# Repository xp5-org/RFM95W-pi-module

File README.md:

# RFM95W-pi-module
PCB to connect RFM95W module to ras pi header

have not tested it yet, need to verify things are wired correctly and pinouts are correct

I set this up to be buildable on a single-layer routed or etched (home made) pcb . 

it relies upon jumper bodge wires to complete some of the wiring, otherwise this would be better served by at least 2 layers or 4 layers board.

ras pi zero has two SPI channels, which can allow up to two simutaenous radios/modems in use. 

<br>
<br>

## single radio layout ##

<br>
<br>

## dual radio layout ##

<br>
<br>

# converting kicad gerbers to G-code for CNC
http://flatcam.org/download

need to generate the isolation path (mill the PCB) and then generate the drill instructions (through-holes and vias drills) separately

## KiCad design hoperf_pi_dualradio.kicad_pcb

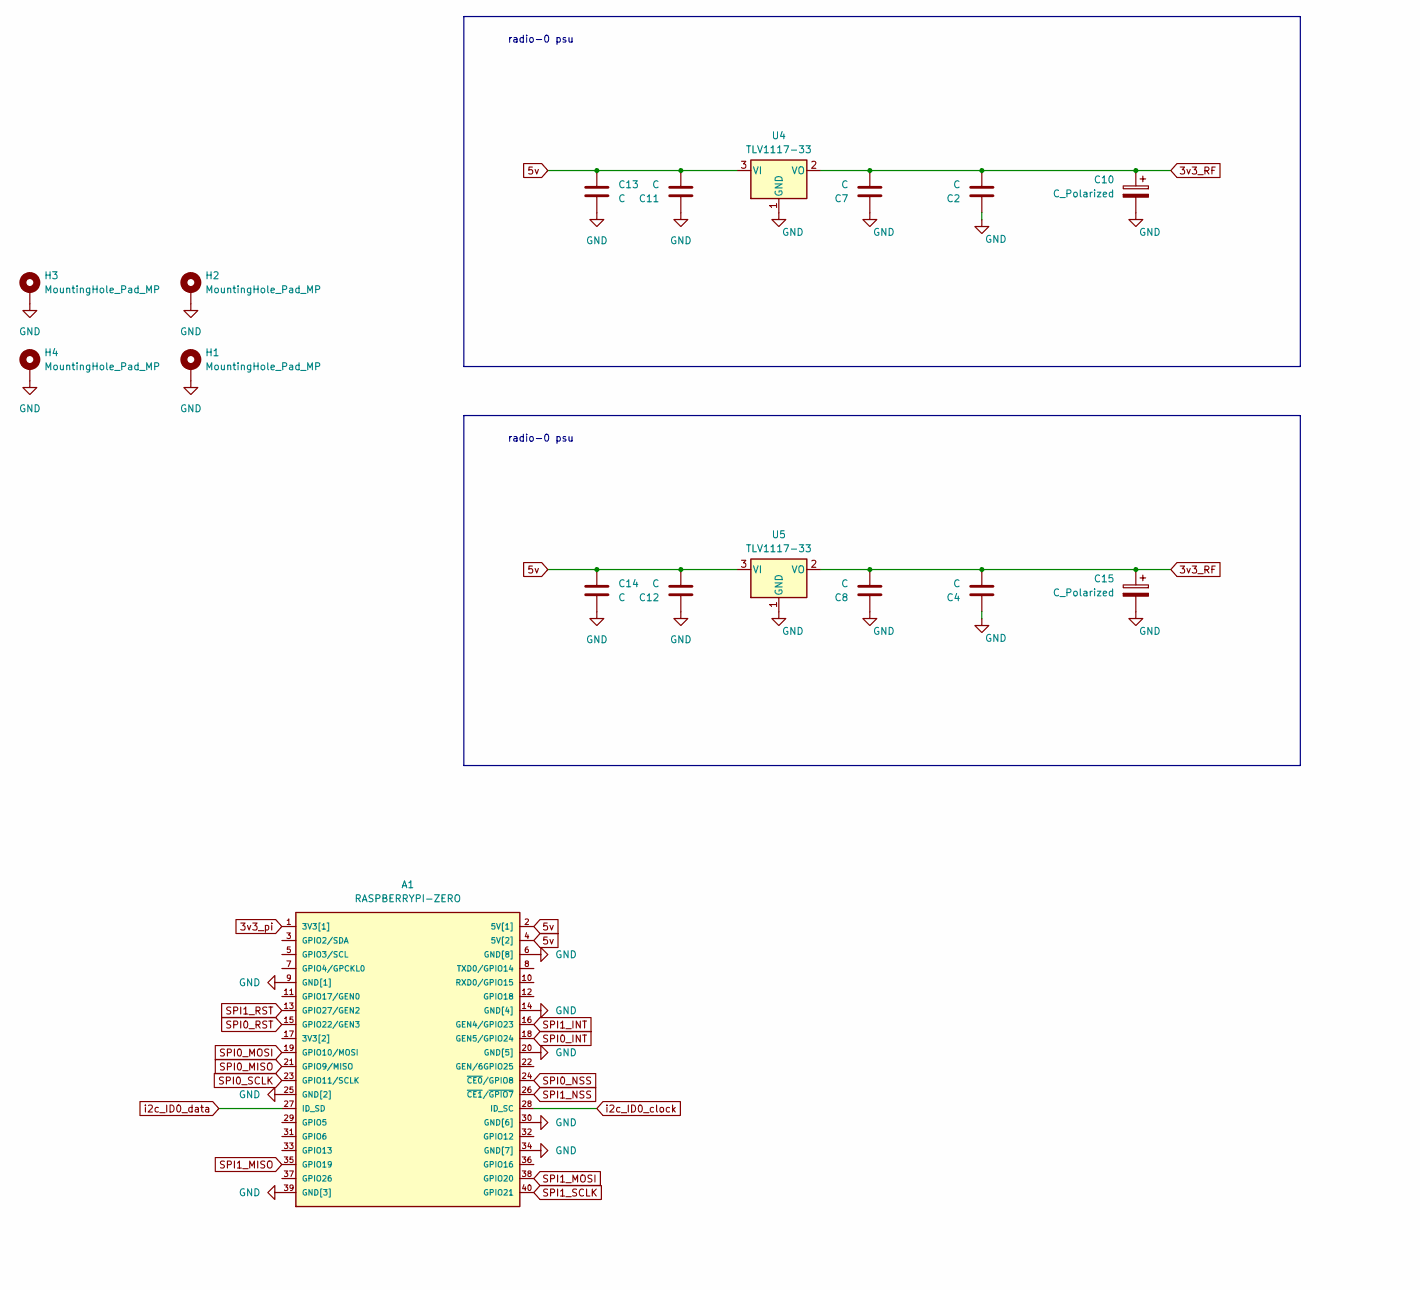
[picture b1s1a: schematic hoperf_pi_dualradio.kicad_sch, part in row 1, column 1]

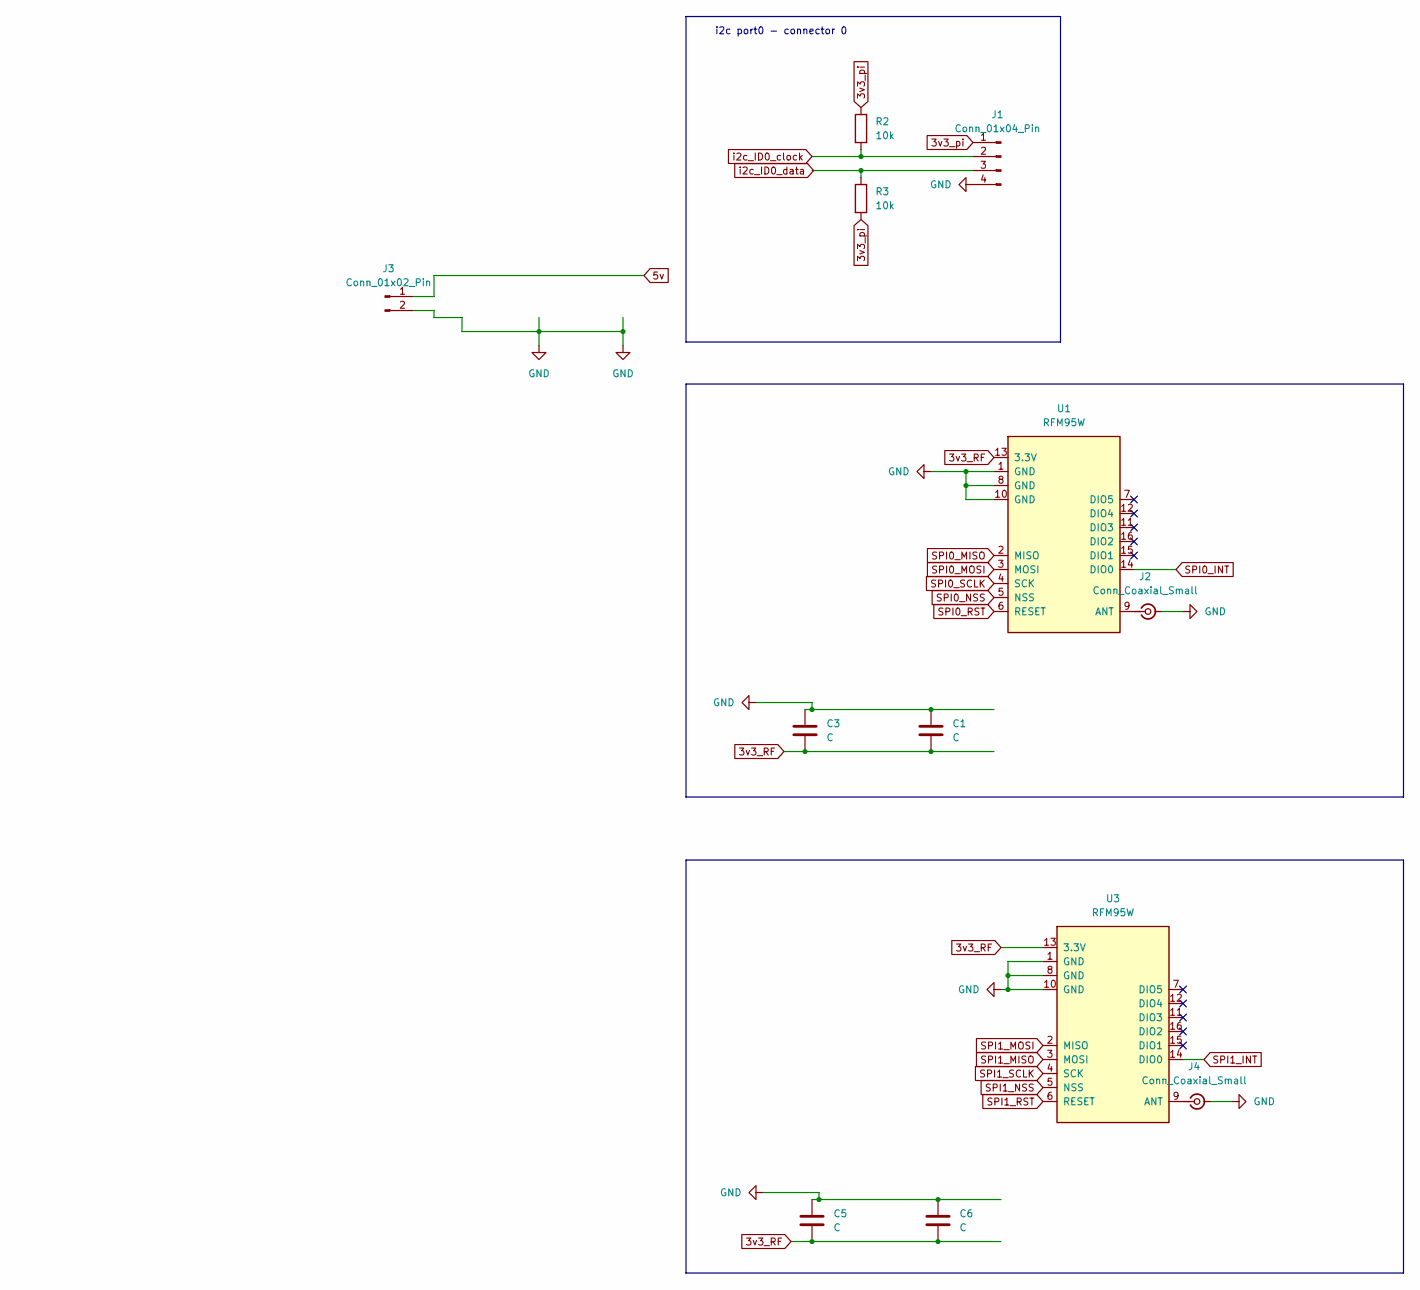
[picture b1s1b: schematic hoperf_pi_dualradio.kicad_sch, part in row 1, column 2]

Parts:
A1: RASPBERRYPI-ZERO; Raspberry_Pi_Zero_Socketed_THT_FaceDown_MountingHoles
C1, C2, C3, C4, C5, C6, C7, C8, C11, C12, C13, C14: C; C_1206_3216Metric
C10, C15: C_Polarized; CP_EIA-7343-43_Kemet-X
H1, H2, H3, H4: MountingHole_Pad_MP; MountingHole_2.5mm_Pad
J1: Conn_01x04_Pin; Molex_PicoBlade_53048-0410_1x04_P1.25mm_Horizontal
J2, J4: Conn_Coaxial_Small; SMA_Amphenol_132289_EdgeMount
J3: Conn_01x02_Pin; PinHeader_1x02_P2.54mm_Horizontal
R2, R3: 10k; R_0603_1608Metric
U1, U3: RFM95W; my_RFM95W
U4, U5: TLV1117-33; SOT-223-3_TabPin2

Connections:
3v3_RF: C1.2, C2.2, C3.2, C4.2, C5.2, C6.2, C7.2, C8.2, C10.1, C15.1, U1.13 (3.3V), U3.13 (3.3V), U4.2 (VO), U5.2 (VO)
3v3_pi: A1.1 (3V3[1]), J1.1, R2.1, R3.2
5v: A1.2 (5V[1]), A1.4 (5V[2]), C11.2, C12.2, C13.1, C14.1, J3.1, U4.3 (VI), U5.3 (VI)
GND: A1.6 (GND[8]), A1.9 (GND[1]), A1.14 (GND[4]), A1.20 (GND[5]), A1.25 (GND[2]), A1.30 (GND[6]), A1.34 (GND[7]), A1.39 (GND[3]), C1.1, C2.1, C3.1, C4.1, C5.1, C6.1, C7.1, C8.1, C10.2, C11.1, C12.1, C13.2, C14.2, C15.2, H1.MP, H2.MP, H3.MP, H4.MP, J1.4, J2.2 (Ext), J3.2, J4.2 (Ext), U1.1 (GND), U1.8 (GND), U1.10 (GND), U3.1 (GND), U3.8 (GND), U3.10 (GND), U4.1 (GND), U5.1 (GND)
unnamed: J2.1 (In), U1.9 (ANT)
unnamed: J4.1 (In), U3.9 (ANT)
SPI0_INT: A1.18 (GEN5/GPIO24), U1.14 (DIO0)
SPI0_MISO: A1.21 (GPIO9/MISO), U1.2 (MISO)
SPI0_MOSI: A1.19 (GPIO10/MOSI), U1.3 (MOSI)
SPI0_NSS: A1.24 (~CE0/GPIO8), U1.5 (NSS)
SPI0_RST: A1.15 (GPIO22/GEN3), U1.6 (RESET)
SPI0_SCLK: A1.23 (GPIO11/SCLK), U1.4 (SCK)
SPI1_INT: A1.16 (GEN4/GPIO23), U3.14 (DIO0)
SPI1_MISO: A1.35 (GPIO19), U3.3 (MOSI)
SPI1_MOSI: A1.38 (GPIO20), U3.2 (MISO)
SPI1_NSS: A1.26 (~CE1/~GPIO7), U3.5 (NSS)
SPI1_RST: A1.13 (GPIO27/GEN2), U3.6 (RESET)
SPI1_SCLK: A1.40 (GPIO21), U3.4 (SCK)
i2c_ID0_clock: A1.28 (ID_SC), J1.2, R2.2
i2c_ID0_data: A1.27 (ID_SD), J1.3, R3.1

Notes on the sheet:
radio-0 psu
i2c port0 - connector 0

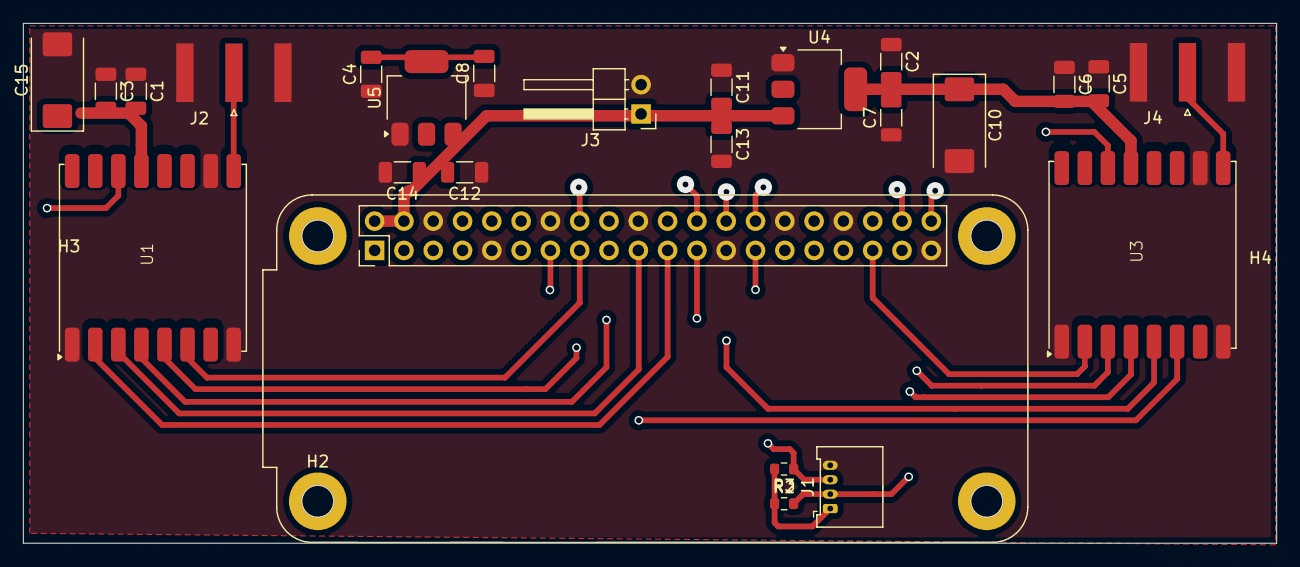
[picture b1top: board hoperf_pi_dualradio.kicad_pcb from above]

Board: 2 copper layers, 108.7 x 45.1 mm, 29 parts (0 on the bottom side), 20 nets.

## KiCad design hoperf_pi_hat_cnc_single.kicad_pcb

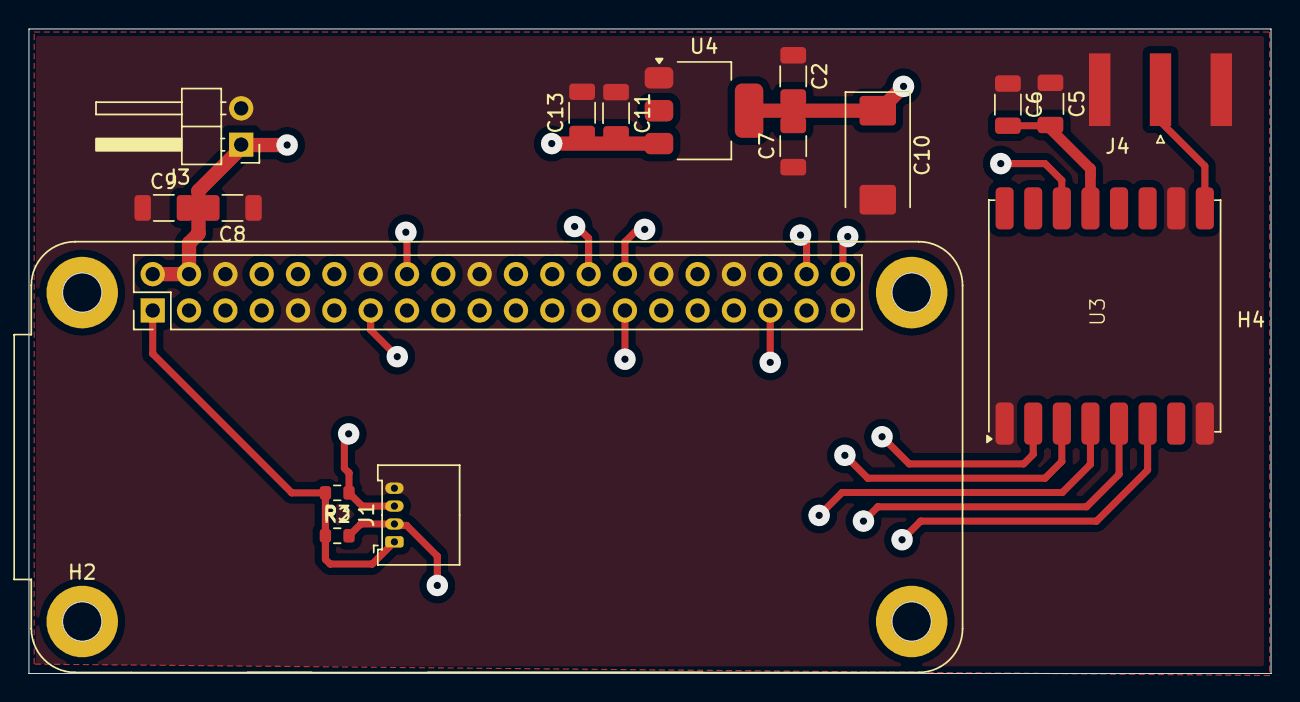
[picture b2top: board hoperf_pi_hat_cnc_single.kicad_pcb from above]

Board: 2 copper layers, 86.9 x 45.1 mm, 21 parts (0 on the bottom side), 13 nets.

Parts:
A1: RASPBERRYPI-ZERO; Raspberry_Pi_Zero_Socketed_THT_FaceDown_MountingHoles
C2, C5, C6, C7, C8, C9, C11, C13: C; C_1206_3216Metric
C10: C_Polarized; CP_EIA-7343-43_Kemet-X
H1, H2, H3, H4: MountingHole_Pad_MP; MountingHole_2.5mm_Pad
J1: Conn_01x04_Pin; Molex_PicoBlade_53048-0410_1x04_P1.25mm_Horizontal
J3: Conn_01x02_Pin; PinHeader_1x02_P2.54mm_Horizontal
J4: Conn_Coaxial_Small; SMA_Amphenol_132289_EdgeMount
R2, R3: 10k; R_0603_1608Metric
U3: RFM95W; my_RFM95W
U4: TLV1117-33; SOT-223-3_TabPin2

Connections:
3v3_RF: C2.2, C5.2, C6.2, C7.2, C10.1, U3.13 (3.3V), U4.2 (VO)
3v3_pi: A1.1 (3V3[1]), J1.1, R2.1, R3.2
5v: A1.2 (5V[1]), A1.4 (5V[2]), C8.2, C9.2, C11.2, C13.1, J3.1, U4.3 (VI)
GND: A1.6 (GND[8]), A1.9 (GND[1]), A1.14 (GND[4]), A1.20 (GND[5]), A1.25 (GND[2]), A1.30 (GND[6]), A1.34 (GND[7]), A1.39 (GND[3]), C2.1, C5.1, C6.1, C7.1, C8.1, C9.1, C10.2, C11.1, C13.2, J1.4, J3.2, J4.2 (Ext), U3.1 (GND), U3.8 (GND), U3.10 (GND), U4.1 (GND)
unnamed: J4.1 (In), U3.9 (ANT)
SPI0_INT: A1.18 (GEN5/GPIO24), U3.14 (DIO0)
SPI0_MISO: A1.21 (GPIO9/MISO), U3.2 (MISO)
SPI0_MOSI: A1.19 (GPIO10/MOSI), U3.3 (MOSI)
SPI0_NSS: A1.24 (~CE0/GPIO8), U3.5 (NSS)
SPI0_RST: A1.15 (GPIO22/GEN3), U3.6 (RESET)
SPI0_SCLK: A1.23 (GPIO11/SCLK), U3.4 (SCK)
i2c_ID0_clock: A1.28 (ID_SC), J1.2, R2.2
i2c_ID0_data: A1.27 (ID_SD), J1.3, R3.1

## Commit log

2025-10-17 added project files
2025-10-17 Update README.md
    added screenshots from kicad
